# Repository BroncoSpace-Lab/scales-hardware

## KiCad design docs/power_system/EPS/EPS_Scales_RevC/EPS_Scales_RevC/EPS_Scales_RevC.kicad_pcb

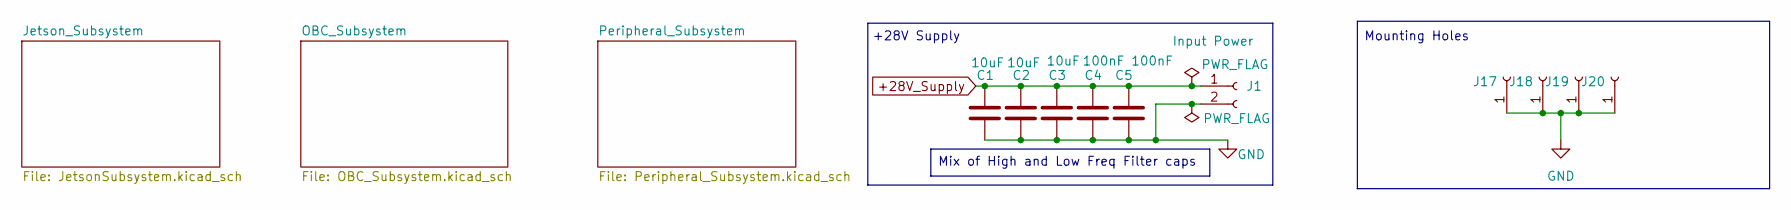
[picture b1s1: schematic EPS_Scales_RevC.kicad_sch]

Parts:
C1, C2, C3: 10uF; C_0603_1608Metric
C4, C5: 100nF; C_0603_1608Metric
J1: Input Power; AMASS_XT60PW-F_1x02_P7.20mm_Horizontal
J17, J18, J19, J20: Conn_01x01_Socket; MountingHole_2.7mm_M2.5_Pad_Via

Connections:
+28V_Supply: C1.1, C2.1, C3.1, C4.1, C5.1, J1.1; also elsewhere on the board
GND: C1.2, C2.2, C3.2, C4.2, C5.2, J1.2, J17.1, J18.1, J19.1, J20.1; also elsewhere on the board

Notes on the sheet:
Mounting Holes
+28V Supply
Mix of High and Low Freq Filter caps

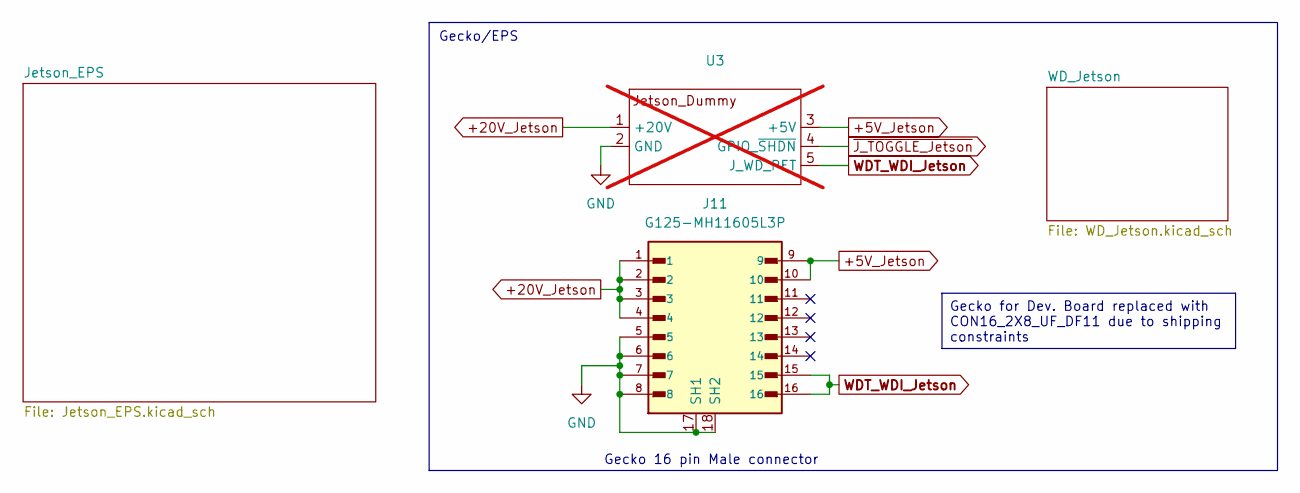
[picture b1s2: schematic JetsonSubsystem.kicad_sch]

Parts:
J11: G125-MH11605L3P; CON16_2X8_UF_DF11
U3: PinSocket_1x05_P2.54mm_Vertical; not fitted

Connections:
+5V_Jetson: J11.9, J11.10, U3.3 (+5V); also elsewhere on the board
+20V_Jetson: J11.1, J11.2, J11.3, J11.4, U3.1 (+20V); also elsewhere on the board
GND: J11.5, J11.6, J11.7, J11.8, J11.17 (SH1), J11.18 (SH2), U3.2 (GND); also elsewhere on the board
WDT_WDI_Jetson: J11.15, J11.16, U3.5 (J_WD_PET); also elsewhere on the board

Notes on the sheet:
Gecko 16 pin Male connector
Gecko/EPS
Gecko for Dev. Board replaced with CON16_2X8_UF_DF11 due to shipping constraints

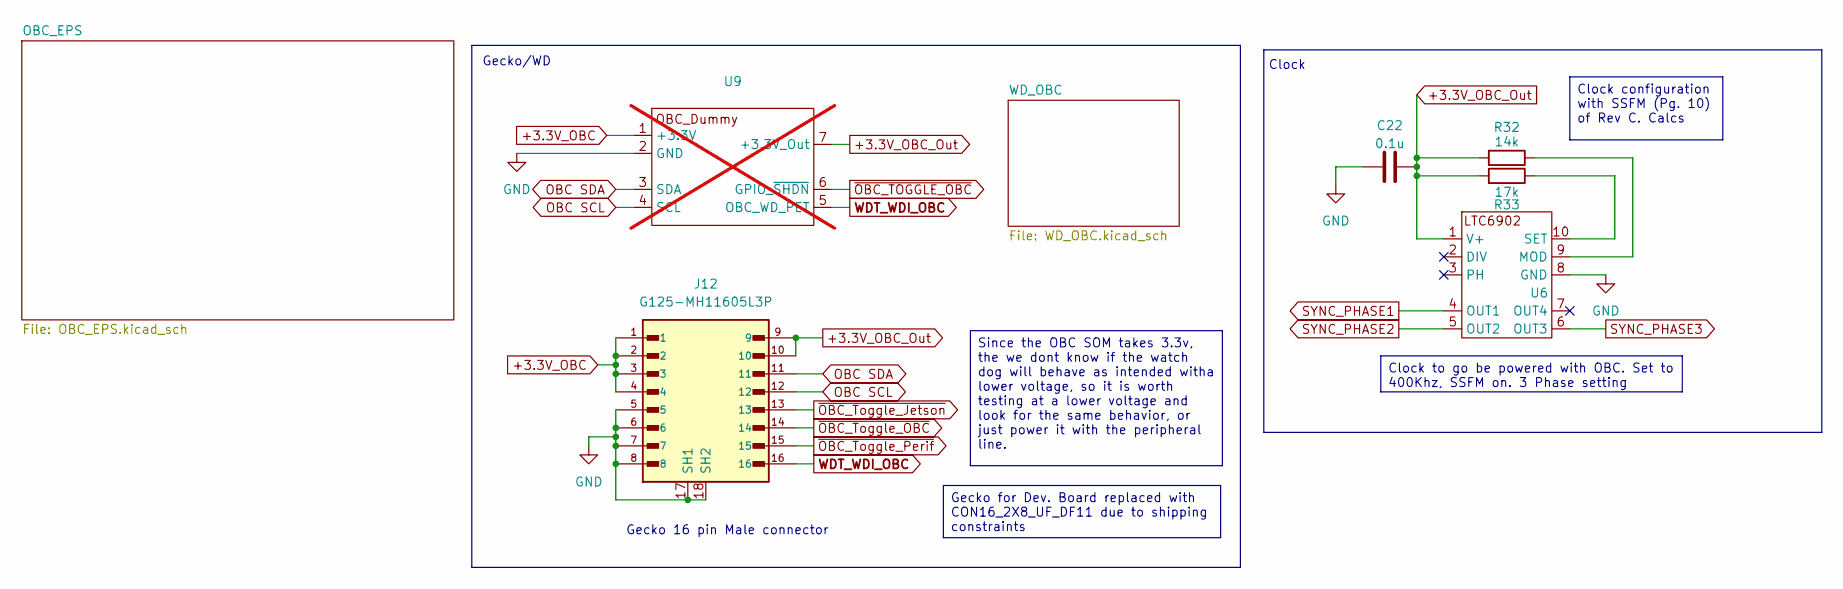
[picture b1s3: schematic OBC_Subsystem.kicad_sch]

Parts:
C22: 0.1u; C_0603_1608Metric
J12: G125-MH11605L3P; CON16_2X8_UF_DF11
R32: 14k; R_0603_1608Metric
R33: 17k; R_0603_1608Metric
U6: LTC6902
U9: PinSocket_1x07_P2.54mm_Vertical; not fitted

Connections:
+3.3V_OBC: J12.1, J12.2, J12.3, J12.4, U9.1 (+3.3V); also elsewhere on the board
+3.3V_OBC_Out: C22.2, J12.9, J12.10, R32.2, R33.2, U6.1 (V+), U9.7 (+3.3V_Out); also elsewhere on the board
GND: C22.1, J12.5, J12.6, J12.7, J12.8, J12.17 (SH1), J12.18 (SH2), U6.8 (GND), U9.2 (GND); also elsewhere on the board
unnamed: R32.1, U6.9 (MOD)
unnamed: R33.1, U6.10 (SET)
OBC SCL: J12.12, U9.4 (SCL); also elsewhere on the board
OBC SDA: J12.11, U9.3 (SDA); also elsewhere on the board
SYNC_PHASE1: U6.4 (OUT1); also elsewhere on the board
SYNC_PHASE2: U6.5 (OUT2); also elsewhere on the board
SYNC_PHASE3: U6.6 (OUT3); also elsewhere on the board
WDT_WDI_OBC: J12.16, U9.5 (OBC_WD_PET); also elsewhere on the board
~J_EN: J12.13; also elsewhere on the board
~OBC_EN: J12.14; also elsewhere on the board
~OBC_Toggle_Perif: J12.15; also elsewhere on the board

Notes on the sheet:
Clock
Gecko/WD
Gecko 16 pin Male connector
Since the OBC SOM takes 3.3v, the we dont know if the watch dog will behave as intended witha lower voltage, so it is worth testing at a lower voltage and look for the same behavior, or just power it with the peripheral line.
Gecko for Dev. Board replaced with CON16_2X8_UF_DF11 due to shipping constraints
Clock configuration with SSFM (Pg. 10) of Rev C. Calcs
Clock to go be powered with OBC. Set to 400Khz, SSFM on. 3 Phase setting

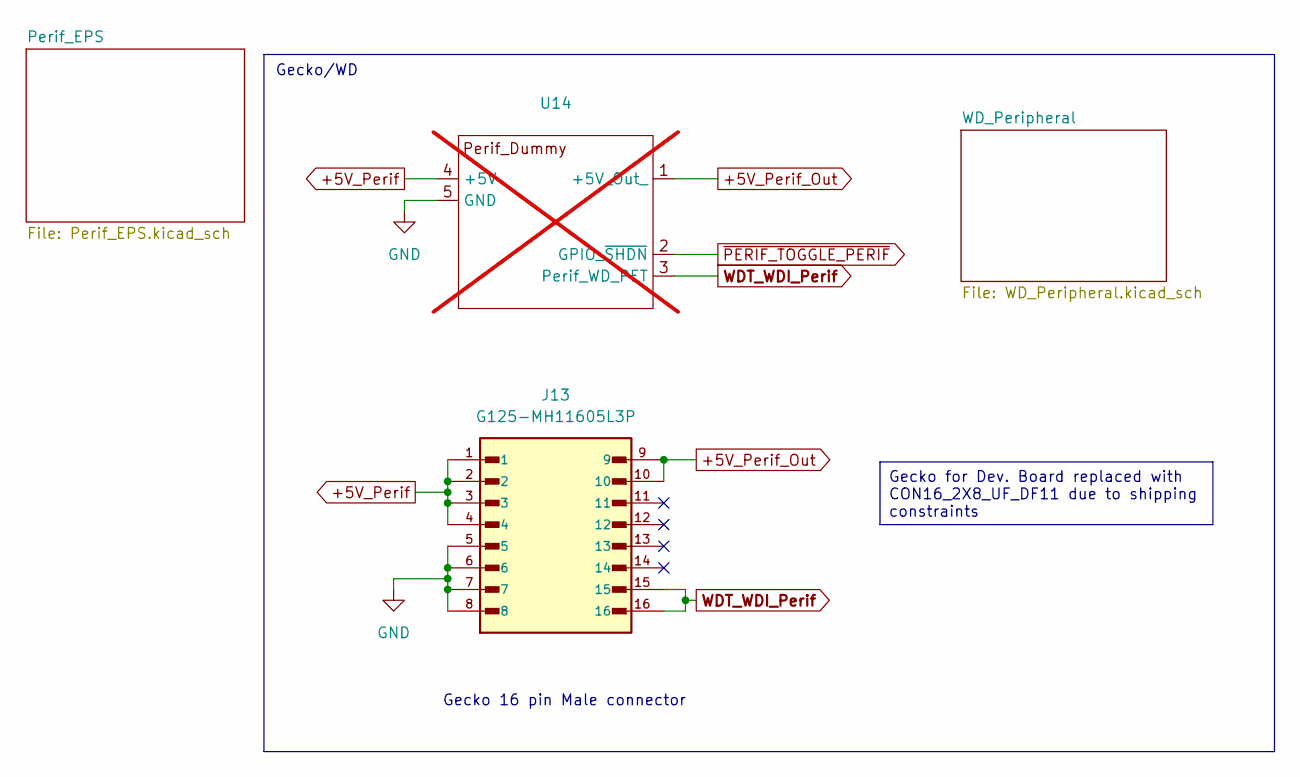
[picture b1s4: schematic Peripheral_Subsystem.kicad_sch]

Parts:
J13: G125-MH11605L3P; CON16_2X8_UF_DF11
U14: Perif. Board Dummy Connections; PinSocket_1x05_P2.54mm_Vertical; not fitted

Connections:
+5V_Perif: J13.1, J13.2, J13.3, J13.4, U14.4 (+5V); also elsewhere on the board
+5V_Perif_Out: J13.9, J13.10, U14.1 (+5V_Out_); also elsewhere on the board
GND: J13.5, J13.6, J13.7, J13.8, U14.5 (GND); also elsewhere on the board
WDT_WDI_Perif: J13.15, J13.16, U14.3 (Perif_WD_PET); also elsewhere on the board

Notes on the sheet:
Gecko/WD
Gecko 16 pin Male connector
Gecko for Dev. Board replaced with CON16_2X8_UF_DF11 due to shipping constraints

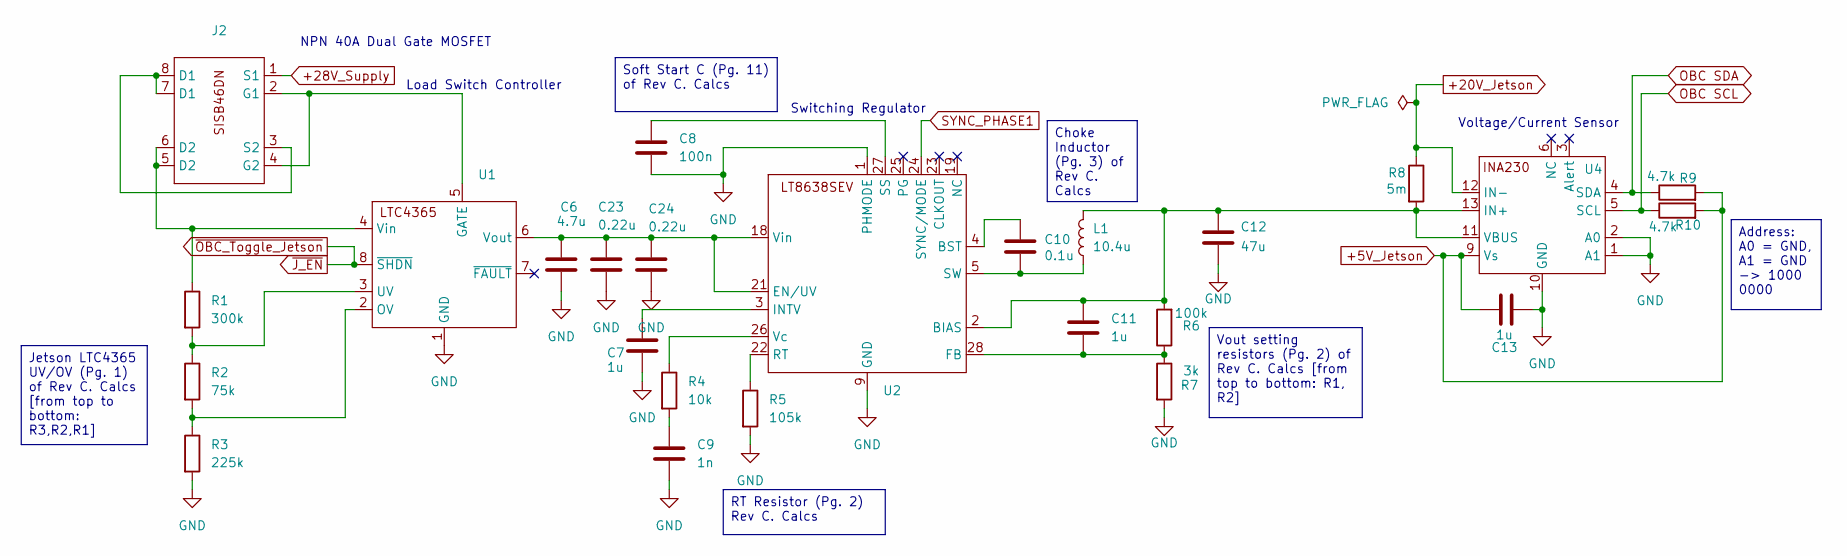
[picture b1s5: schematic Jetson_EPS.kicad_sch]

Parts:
C6: 4.7u; C_0603_1608Metric
C7, C11, C13: 1u; C_0603_1608Metric
C8: 100n; C_0603_1608Metric
C9: 1n; C_0603_1608Metric
C10: 0.1u; C_0603_1608Metric
C12: 47u; C_0603_1608Metric
C23, C24: 0.22u; C_0603_1608Metric
J2: MOSFET_DN-T1-GE3_VIS
L1: 10.4u; L_0603_1608Metric
R1: 300k; R_0603_1608Metric
R2: 75k; R_0603_1608Metric
R3: 225k; R_0603_1608Metric
R4: 10k; R_0603_1608Metric
R5: 105k; R_0603_1608Metric
R6: 100k; R_0603_1608Metric
R7: 3k; R_0603_1608Metric
R8: 5m; R_0603_1608Metric
R9, R10: 4.7k; R_0603_1608Metric
U1: LTC4365
U2: LT8638SEVPBF
U4: INA230; INA230AIRGTT

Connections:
+5V_Jetson: C13.2, R9.2, R10.2, U4.9 (Vs); also elsewhere on the board
+20V_Jetson: R8.1, U4.12 (IN-); also elsewhere on the board
+28V_Supply: J2.1 (S1); also elsewhere on the board
GND: C6.2, C7.2, C8.2, C9.2, C12.2, C13.1, C23.2, C24.2, R3.2, R5.2, R7.2, U1.1 (GND), U2.1 (PHMODE), U2.9 (GND), U4.1 (A1), U4.2 (A0), U4.10 (GND); also elsewhere on the board
unnamed: C9.1, R4.2
unnamed: J2.2 (G1), J2.4 (G2), U1.5 (GATE)
unnamed: J2.3 (S2), J2.7 (D1), J2.8 (D1)
unnamed: R2.2, R3.1, U1.2 (OV)
unnamed: R1.2, R2.1, U1.3 (UV)
unnamed: J2.5 (D2), J2.6 (D2), R1.1, U1.4 (Vin)
unnamed: C6.1, C23.1, C24.1, U1.6 (Vout), U2.18 (Vin), U2.21 (EN/UV)
unnamed: C11.1, C12.1, L1.2, R6.2, R8.2, U2.2 (BIAS), U4.11 (VBUS), U4.13 (IN+)
unnamed: C10.1, U2.4 (BST)
unnamed: C11.2, R6.1, R7.1, U2.28 (FB)
unnamed: C7.1, U2.3 (INTV)
unnamed: R5.1, U2.22 (RT)
unnamed: C8.1, U2.27 (SS)
unnamed: C10.2, L1.1, U2.5 (SW)
unnamed: R4.1, U2.26 (Vc)
OBC SCL: R10.1, U4.5 (SCL); also elsewhere on the board
OBC SDA: R9.1, U4.4 (SDA); also elsewhere on the board
SYNC_PHASE1: U2.24 (SYNC/MODE); also elsewhere on the board
~J_EN: U1.8 (~SHDN); also elsewhere on the board

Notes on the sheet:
Voltage/Current Sensor
Load Switch Controller
Switching Regulator
NPN 40A Dual Gate MOSFET
RT Resistor (Pg. 2) Rev C. Calcs
Jetson LTC4365 UV/OV (Pg. 1) of Rev C. Calcs [from top to bottom: R3,R2,R1]
Vout setting resistors (Pg. 2) of Rev C. Calcs [from top to bottom: R1, R2]
Choke Inductor (Pg. 3) of Rev C. Calcs
Address: A0 = GND, A1 = GND -> 1000 0000
Soft Start C (Pg. 11) of Rev C. Calcs

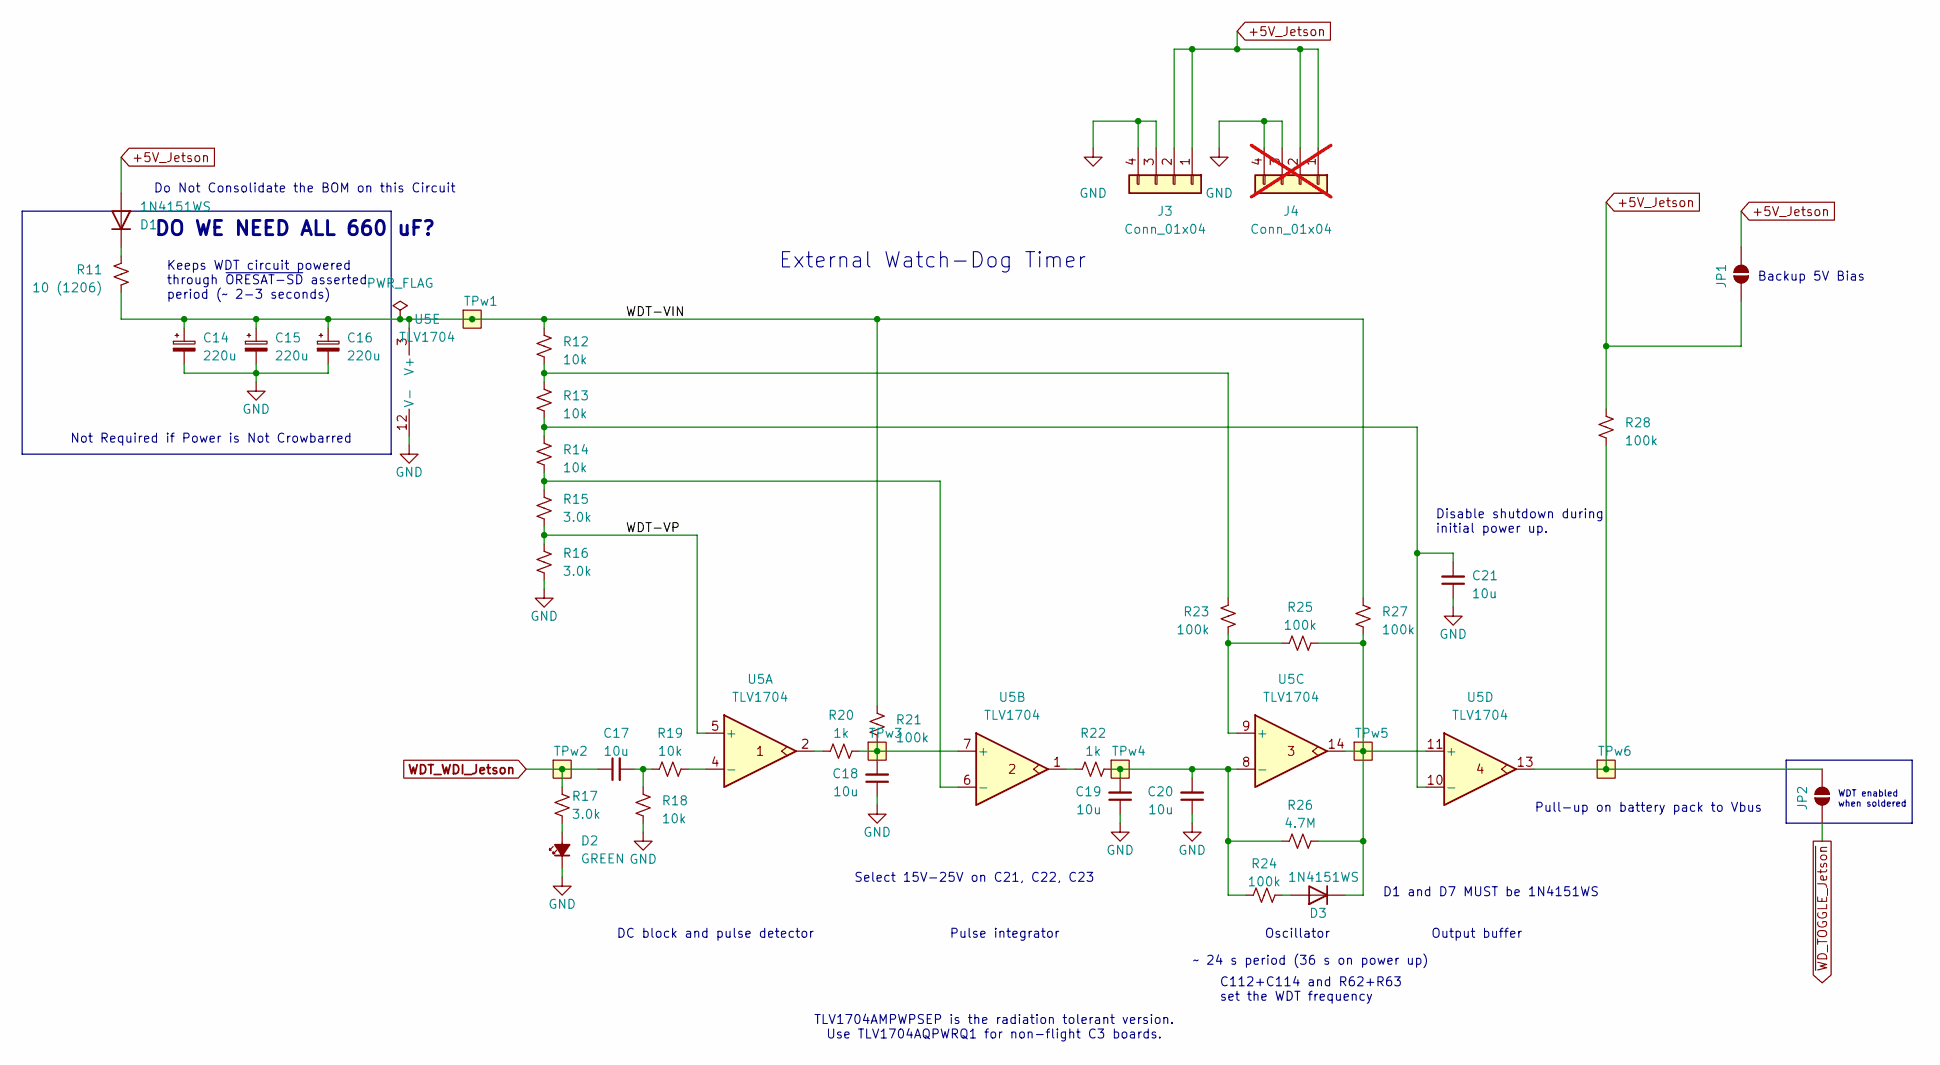
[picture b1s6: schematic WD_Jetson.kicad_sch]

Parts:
C14, C15, C16: 220u; CP_EIA-7361-38_AVX-V; MPN TCN4227M025R0100
C17, C18, C19, C20, C21: 10u; C_0603_1608Metric; MPN GRT188R61C106KE13D
D1, D3: 1N4151WS; D_SOD-323; MPN 1N4151WS-E3-08
D2: GREEN; LED_0603_1608Metric; MPN 150060GS75000
J3: Conn_01x04; PinSocket_1x04_P2.54mm_Vertical
J4: Conn_01x04; PinSocket_1x04_P2.54mm_Vertical; not fitted
JP1, JP2: SolderJumper_2_Open; SolderJumper-2_P1.3mm_Open_RoundedPad1.0x1.5mm
R11: 10 (1206); R_1206_3216Metric; MPN ESR18EZPF10R0
R12, R13, R14, R18, R19: 10k; R_0603_1608Metric; MPN RMCF0603FT10K0
R15, R16, R17: 3.0k; R_0603_1608Metric; MPN RMCF0603FT3K00
R20, R22: 1k; R_0603_1608Metric; MPN RMCF0603FT1K00
R21, R23, R24, R25, R27, R28: 100k; R_0603_1608Metric; MPN RMCF0603FT100K
R26: 4.7M; R_0603_1608Metric; MPN RMCF0603FT4M70
TPw1, TPw2, TPw3, TPw4, TPw5, TPw6: TestPoint-MinTH; TestPoint_Pad_1.0x1.0mm
U5: TLV1704; TSSOP-14_4.4x5mm_P0.65mm; MPN TLV1704AQPWRQ1

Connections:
+5V_Jetson: D1.2 (A), J3.1, J3.2, J4.1, J4.2, JP1.1 (A), JP1.2 (B), R28.2; also elsewhere on the board
/Jetson_Subsystem/WD_Jetson/WDT-VIN: C14.1, C15.1, C16.1, R11.2, R12.1, R21.1, R27.2, TPw1.1, U5.3 (V+)
/Jetson_Subsystem/WD_Jetson/WDT-VP: R15.2, R16.1, U5.5 (+)
GND: C14.2, C15.2, C16.2, C18.1, C19.1, C20.1, C21.1, D2.1 (K), J3.3, J3.4, J4.3, J4.4, R16.2, R18.2, U5.12 (V-); also elsewhere on the board
unnamed: C17.2, R18.1, R19.1
unnamed: D1.1 (K), R11.1
unnamed: D2.2 (A), R17.2
unnamed: D3.2 (A), R24.1
unnamed: D3.1 (K), R25.2, R26.1, R27.1, TPw5.1, U5.11 (+), U5.14
unnamed: JP2.1 (A), R28.1, TPw6.1, U5.13
unnamed: R12.2, R13.1, R23.2
unnamed: R20.1, U5.2
unnamed: R22.1, U5.1
unnamed: R19.2, U5.4 (-)
unnamed: C18.2, R20.2, R21.2, TPw3.1, U5.7 (+)
unnamed: R14.2, R15.1, U5.6 (-)
unnamed: R23.1, R25.1, U5.9 (+)
unnamed: C19.2, C20.2, R22.2, R24.2, R26.2, TPw4.1, U5.8 (-)
unnamed: C21.2, R13.2, R14.1, U5.10 (-)
WDT_WDI_Jetson: C17.1, R17.1, TPw2.1; also elsewhere on the board
~WD_TOGGLE_Jetson: JP2.2 (B)

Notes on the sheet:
TLV1704AMPWPSEP is the radiation tolerant version. Use TLV1704AQPWRQ1 for non-flight C3 boards.
Keeps WDT circuit powered through ~{ORESAT-SD} asserted period (~ 2-3 seconds)
Backup 5V Bias
Pull-up on battery pack to Vbus
Oscillator
External Watch-Dog Timer
Disable shutdown during initial power up.
Not Required if Power is Not Crowbarred
Pulse integrator
C112+C114 and R62+R63 set the WDT frequency
DO WE NEED ALL 660 uF?
~ 24 s period (36 s on power up)
D1 and D7 MUST be 1N4151WS
Do Not Consolidate the BOM on this Circuit
Select 15V-25V on C21, C22, C23
Output buffer
WDT enabled when soldered
DC block and pulse detector

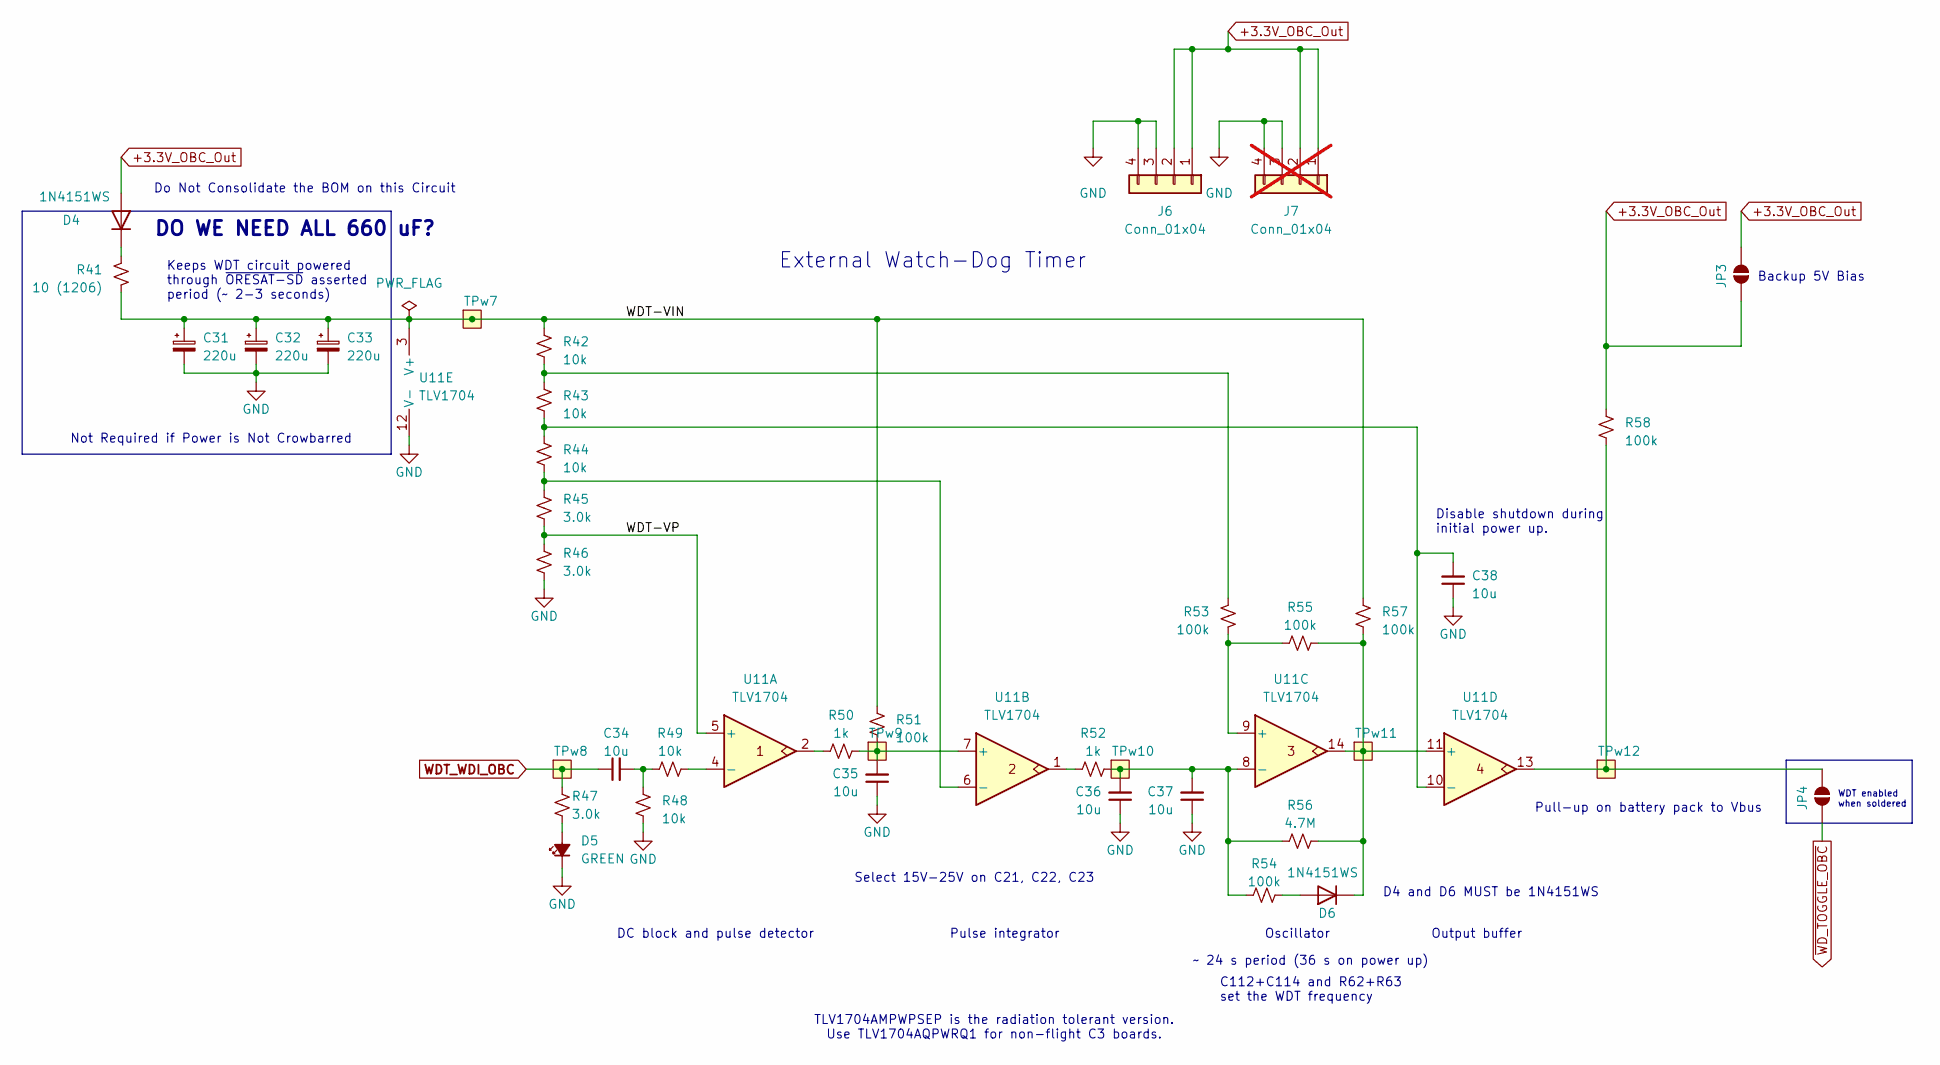
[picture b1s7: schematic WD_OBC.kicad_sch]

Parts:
C31, C32, C33: 220u; CP_EIA-7361-38_AVX-V; MPN TCN4227M025R0100
C34, C35, C36, C37, C38: 10u; C_0603_1608Metric; MPN GRT188R61C106KE13D
D4, D6: 1N4151WS; D_SOD-323; MPN 1N4151WS-E3-08
D5: GREEN; LED_0603_1608Metric; MPN 150060GS75000
J6: Conn_01x04; PinSocket_1x04_P2.54mm_Vertical
J7: Conn_01x04; PinSocket_1x04_P2.54mm_Vertical; not fitted
JP3, JP4: SolderJumper_2_Open; SolderJumper-2_P1.3mm_Open_RoundedPad1.0x1.5mm
R41: 10 (1206); R_1206_3216Metric; MPN ESR18EZPF10R0
R42, R43, R44, R48, R49: 10k; R_0603_1608Metric; MPN RMCF0603FT10K0
R45, R46, R47: 3.0k; R_0603_1608Metric; MPN RMCF0603FT3K00
R50, R52: 1k; R_0603_1608Metric; MPN RMCF0603FT1K00
R51, R53, R54, R55, R57, R58: 100k; R_0603_1608Metric; MPN RMCF0603FT100K
R56: 4.7M; R_0603_1608Metric; MPN RMCF0603FT4M70
TPw7, TPw8, TPw9, TPw10, TPw11, TPw12: TestPoint-MinTH; TestPoint_Pad_1.0x1.0mm
U11: TLV1704; TSSOP-14_4.4x5mm_P0.65mm; MPN TLV1704AQPWRQ1

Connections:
+3.3V_OBC_Out: D4.2 (A), J6.1, J6.2, J7.1, J7.2, JP3.1 (A), JP3.2 (B), R58.2; also elsewhere on the board
/OBC_Subsystem/WD_OBC/WDT-VIN: C31.1, C32.1, C33.1, R41.2, R42.1, R51.1, R57.2, TPw7.1, U11.3 (V+)
/OBC_Subsystem/WD_OBC/WDT-VP: R45.2, R46.1, U11.5 (+)
GND: C31.2, C32.2, C33.2, C35.1, C36.1, C37.1, C38.1, D5.1 (K), J6.3, J6.4, J7.3, J7.4, R46.2, R48.2, U11.12 (V-); also elsewhere on the board
unnamed: C34.2, R48.1, R49.1
unnamed: D4.1 (K), R41.1
unnamed: D5.2 (A), R47.2
unnamed: D6.2 (A), R54.1
unnamed: D6.1 (K), R55.2, R56.1, R57.1, TPw11.1, U11.11 (+), U11.14
unnamed: JP4.1 (A), R58.1, TPw12.1, U11.13
unnamed: R42.2, R43.1, R53.2
unnamed: R50.1, U11.2
unnamed: R52.1, U11.1
unnamed: R49.2, U11.4 (-)
unnamed: C35.2, R50.2, R51.2, TPw9.1, U11.7 (+)
unnamed: R44.2, R45.1, U11.6 (-)
unnamed: R53.1, R55.1, U11.9 (+)
unnamed: C36.2, C37.2, R52.2, R54.2, R56.2, TPw10.1, U11.8 (-)
unnamed: C38.2, R43.2, R44.1, U11.10 (-)
WDT_WDI_OBC: C34.1, R47.1, TPw8.1; also elsewhere on the board
~WD_TOGGLE_OBC: JP4.2 (B)

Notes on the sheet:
TLV1704AMPWPSEP is the radiation tolerant version. Use TLV1704AQPWRQ1 for non-flight C3 boards.
Keeps WDT circuit powered through ~{ORESAT-SD} asserted period (~ 2-3 seconds)
Backup 5V Bias
Pull-up on battery pack to Vbus
Oscillator
External Watch-Dog Timer
Disable shutdown during initial power up.
Not Required if Power is Not Crowbarred
Pulse integrator
C112+C114 and R62+R63 set the WDT frequency
DO WE NEED ALL 660 uF?
~ 24 s period (36 s on power up)
D4 and D6 MUST be 1N4151WS
Do Not Consolidate the BOM on this Circuit
Select 15V-25V on C21, C22, C23
Output buffer
WDT enabled when soldered
DC block and pulse detector

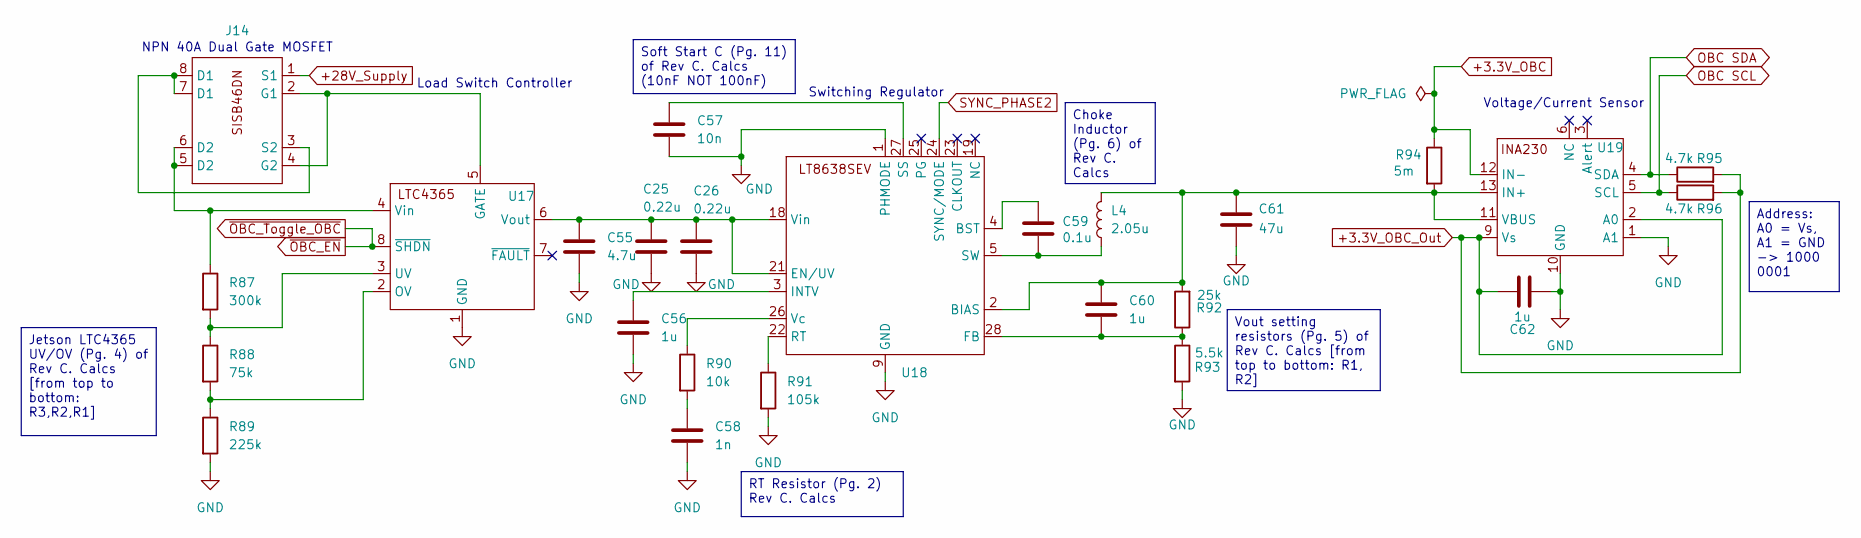
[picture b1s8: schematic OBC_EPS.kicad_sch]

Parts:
C25, C26: 0.22u; C_0603_1608Metric
C55: 4.7u; C_0603_1608Metric
C56, C60, C62: 1u; C_0603_1608Metric
C57: 10n; C_0603_1608Metric
C58: 1n; C_0603_1608Metric
C59: 0.1u; C_0603_1608Metric
C61: 47u; C_0603_1608Metric
J14: MOSFET_DN-T1-GE3_VIS
L4: 2.05u; L_0603_1608Metric
R87: 300k; R_0603_1608Metric
R88: 75k; R_0603_1608Metric
R89: 225k; R_0603_1608Metric
R90: 10k; R_0603_1608Metric
R91: 105k; R_0603_1608Metric
R92: 25k; R_0603_1608Metric
R93: 5.5k; R_0603_1608Metric
R94: 5m; R_0603_1608Metric
R95, R96: 4.7k; R_0603_1608Metric
U17: LTC4365
U18: LT8638SEVPBF
U19: INA230; INA230AIRGTT

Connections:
+3.3V_OBC: R94.1, U19.12 (IN-); also elsewhere on the board
+3.3V_OBC_Out: C62.2, R95.2, R96.2, U19.2 (A0), U19.9 (Vs); also elsewhere on the board
+28V_Supply: J14.1 (S1); also elsewhere on the board
GND: C25.2, C26.2, C55.2, C56.2, C57.2, C58.2, C61.2, C62.1, R89.2, R91.2, R93.2, U17.1 (GND), U18.1 (PHMODE), U18.9 (GND), U19.1 (A1), U19.10 (GND); also elsewhere on the board
unnamed: C58.1, R90.2
unnamed: J14.2 (G1), J14.4 (G2), U17.5 (GATE)
unnamed: J14.3 (S2), J14.7 (D1), J14.8 (D1)
unnamed: R88.2, R89.1, U17.2 (OV)
unnamed: R87.2, R88.1, U17.3 (UV)
unnamed: J14.5 (D2), J14.6 (D2), R87.1, U17.4 (Vin)
unnamed: C25.1, C26.1, C55.1, U17.6 (Vout), U18.18 (Vin), U18.21 (EN/UV)
unnamed: C60.1, C61.1, L4.2, R92.2, R94.2, U18.2 (BIAS), U19.11 (VBUS), U19.13 (IN+)
unnamed: C59.1, U18.4 (BST)
unnamed: C60.2, R92.1, R93.1, U18.28 (FB)
unnamed: C56.1, U18.3 (INTV)
unnamed: R91.1, U18.22 (RT)
unnamed: C57.1, U18.27 (SS)
unnamed: C59.2, L4.1, U18.5 (SW)
unnamed: R90.1, U18.26 (Vc)
OBC SCL: R96.1, U19.5 (SCL); also elsewhere on the board
OBC SDA: R95.1, U19.4 (SDA); also elsewhere on the board
SYNC_PHASE2: U18.24 (SYNC/MODE); also elsewhere on the board
~OBC_EN: U17.8 (~SHDN); also elsewhere on the board

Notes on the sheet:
Switching Regulator
Voltage/Current Sensor
NPN 40A Dual Gate MOSFET
Load Switch Controller
Soft Start C (Pg. 11) of Rev C. Calcs (10nF NOT 100nF)
RT Resistor (Pg. 2) Rev C. Calcs
Choke Inductor (Pg. 6) of Rev C. Calcs
Vout setting resistors (Pg. 5) of Rev C. Calcs [from top to bottom: R1, R2]
Jetson LTC4365 UV/OV (Pg. 4) of Rev C. Calcs [from top to bottom: R3,R2,R1]
Address: A0 = Vs, A1 = GND -> 1000 0001

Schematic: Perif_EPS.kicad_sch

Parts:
C27, C28: 0.22u; C_0603_1608Metric
C63: 4.7u; C_0603_1608Metric
C64, C68, C70: 1u; C_0603_1608Metric
C65: 20nF; C_0603_1608Metric
C66: 1n; C_0603_1608Metric
C67: 0.1u; C_0603_1608Metric
C69: 47u; C_0603_1608Metric
J15: MOSFET_DN-T1-GE3_VIS
L5: 2.9u; L_0603_1608Metric
R97: 300k; R_0603_1608Metric
R98: 75k; R_0603_1608Metric
R99: 225k; R_0603_1608Metric
R100: 10k; R_0603_1608Metric
R101: 105k; R_0603_1608Metric
R102: 22k; R_0603_1608Metric
R103: 3k; R_0603_1608Metric
R104: 5m; R_0603_1608Metric
R105, R106: 4.7k; R_0603_1608Metric
U20: LTC4365
U21: LT8638SEVPBF
U22: INA230; INA230AIRGTT

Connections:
+5V_Perif: R104.1, U22.12 (IN-); also elsewhere on the board
+5V_Perif_Out: C70.2, R105.2, R106.2, U22.9 (Vs); also elsewhere on the board
+28V_Supply: J15.1 (S1); also elsewhere on the board
GND: C27.2, C28.2, C63.2, C64.2, C65.2, C66.2, C69.2, C70.1, R99.2, R101.2, R103.2, U20.1 (GND), U21.1 (PHMODE), U21.9 (GND), U22.1 (A1), U22.10 (GND); also elsewhere on the board
unnamed: C66.1, R100.2
unnamed: J15.2 (G1), J15.4 (G2), U20.5 (GATE)
unnamed: J15.3 (S2), J15.7 (D1), J15.8 (D1)
unnamed: R98.2, R99.1, U20.2 (OV)
unnamed: R97.2, R98.1, U20.3 (UV)
unnamed: J15.5 (D2), J15.6 (D2), R97.1, U20.4 (Vin)
unnamed: C27.1, C28.1, C63.1, U20.6 (Vout), U21.18 (Vin), U21.21 (EN/UV)
unnamed: C68.1, C69.1, L5.2, R102.2, R104.2, U21.2 (BIAS), U22.11 (VBUS), U22.13 (IN+)
unnamed: C67.1, U21.4 (BST)
unnamed: C68.2, R102.1, R103.1, U21.28 (FB)
unnamed: C64.1, U21.3 (INTV)
unnamed: R101.1, U21.22 (RT)
unnamed: C65.1, U21.27 (SS)
unnamed: C67.2, L5.1, U21.5 (SW)
unnamed: R100.1, U21.26 (Vc)
OBC SCL: R106.1, U22.5 (SCL); also elsewhere on the board
OBC SDA: R105.1, U22.2 (A0), U22.4 (SDA); also elsewhere on the board
SYNC_PHASE3: U21.24 (SYNC/MODE); also elsewhere on the board
~OBC_Toggle_Perif: U20.8 (~SHDN); also elsewhere on the board

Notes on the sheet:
Voltage/Current Sensor
NPN 40A Dual Gate MOSFET
Load Switch Controller
Switching Regulator
Vout setting resistors (Pg. 5) of Rev C. Calcs [from top to bottom: R1, R2]
Peripheral LTC4365 UV/OV (Pg. 7) of Rev C. Calcs [from top to bottom: R3,R2,R1]
RT Resistor (Pg. 2) Rev C. Calcs
Soft Start C (Pg. 11) of Rev C. Calcs
Choke Inductor (Pg. 9) of Rev C. Calcs
Address: A0 = SDA, A1 = GND -> 1000 0010

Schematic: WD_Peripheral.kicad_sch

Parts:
C47, C48, C49: 220u; CP_EIA-7361-38_AVX-V; MPN TCN4227M025R0100
C50, C51, C52, C53, C54: 10u; C_0603_1608Metric; MPN GRT188R61C106KE13D
D7, D9: 1N4151WS; D_SOD-323; MPN 1N4151WS-E3-08
D8: GREEN; LED_0603_1608Metric; MPN 150060GS75000
J9: Conn_01x04; PinSocket_1x04_P2.54mm_Vertical
J10: Conn_01x04; PinSocket_1x04_P2.54mm_Vertical; not fitted
JP5, JP6: SolderJumper_2_Open; SolderJumper-2_P1.3mm_Open_RoundedPad1.0x1.5mm
R69: 10 (1206); R_1206_3216Metric; MPN ESR18EZPF10R0
R70, R71, R72, R76, R77: 10k; R_0603_1608Metric; MPN RMCF0603FT10K0
R73, R74, R75: 3.0k; R_0603_1608Metric; MPN RMCF0603FT3K00
R78, R80: 1k; R_0603_1608Metric; MPN RMCF0603FT1K00
R79, R81, R82, R83, R85, R86: 100k; R_0603_1608Metric; MPN RMCF0603FT100K
R84: 4.7M; R_0603_1608Metric; MPN RMCF0603FT4M70
TPw13, TPw14, TPw15, TPw16, TPw17, TPw18: TestPoint-MinTH; TestPoint_Pad_1.0x1.0mm
U16: TLV1704; TSSOP-14_4.4x5mm_P0.65mm; MPN TLV1704AQPWRQ1

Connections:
+5V_Perif_Out: D7.2 (A), J9.1, J9.2, J10.1, J10.2, JP5.1 (A), JP5.2 (B), R86.2; also elsewhere on the board
/Peripheral_Subsystem/WD_Peripheral/WDT-VIN: C47.1, C48.1, C49.1, R69.2, R70.1, R79.1, R85.2, TPw13.1, U16.3 (V+)
/Peripheral_Subsystem/WD_Peripheral/WDT-VP: R73.2, R74.1, U16.5 (+)
GND: C47.2, C48.2, C49.2, C51.1, C52.1, C53.1, C54.1, D8.1 (K), J9.3, J9.4, J10.3, J10.4, R74.2, R76.2, U16.12 (V-); also elsewhere on the board
unnamed: C50.2, R76.1, R77.1
unnamed: D7.1 (K), R69.1
unnamed: D8.2 (A), R75.2
unnamed: D9.2 (A), R82.1
unnamed: D9.1 (K), R83.2, R84.1, R85.1, TPw17.1, U16.11 (+), U16.14
unnamed: JP6.1 (A), R86.1, TPw18.1, U16.13
unnamed: R70.2, R71.1, R81.2
unnamed: R78.1, U16.2
unnamed: R80.1, U16.1
unnamed: R77.2, U16.4 (-)
unnamed: C51.2, R78.2, R79.2, TPw15.1, U16.7 (+)
unnamed: R72.2, R73.1, U16.6 (-)
unnamed: R81.1, R83.1, U16.9 (+)
unnamed: C52.2, C53.2, R80.2, R82.2, R84.2, TPw16.1, U16.8 (-)
unnamed: C54.2, R71.2, R72.1, U16.10 (-)
WDT_WDI_Perif: C50.1, R75.1, TPw14.1; also elsewhere on the board
~OBC_Toggle_Perif: JP6.2 (B); also elsewhere on the board

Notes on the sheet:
TLV1704AMPWPSEP is the radiation tolerant version. Use TLV1704AQPWRQ1 for non-flight C3 boards.
Keeps WDT circuit powered through ~{ORESAT-SD} asserted period (~ 2-3 seconds)
Backup 5V Bias
Pull-up on battery pack to Vbus
Oscillator
External Watch-Dog Timer
Disable shutdown during initial power up.
Not Required if Power is Not Crowbarred
Pulse integrator
C112+C114 and R62+R63 set the WDT frequency
DO WE NEED ALL 660 uF?
~ 24 s period (36 s on power up)
D5 and D7 MUST be 1N4151WS
Do Not Consolidate the BOM on this Circuit
Select 15V-25V on C21, C22, C23
Output buffer
WDT enabled when soldered
DC block and pulse detector

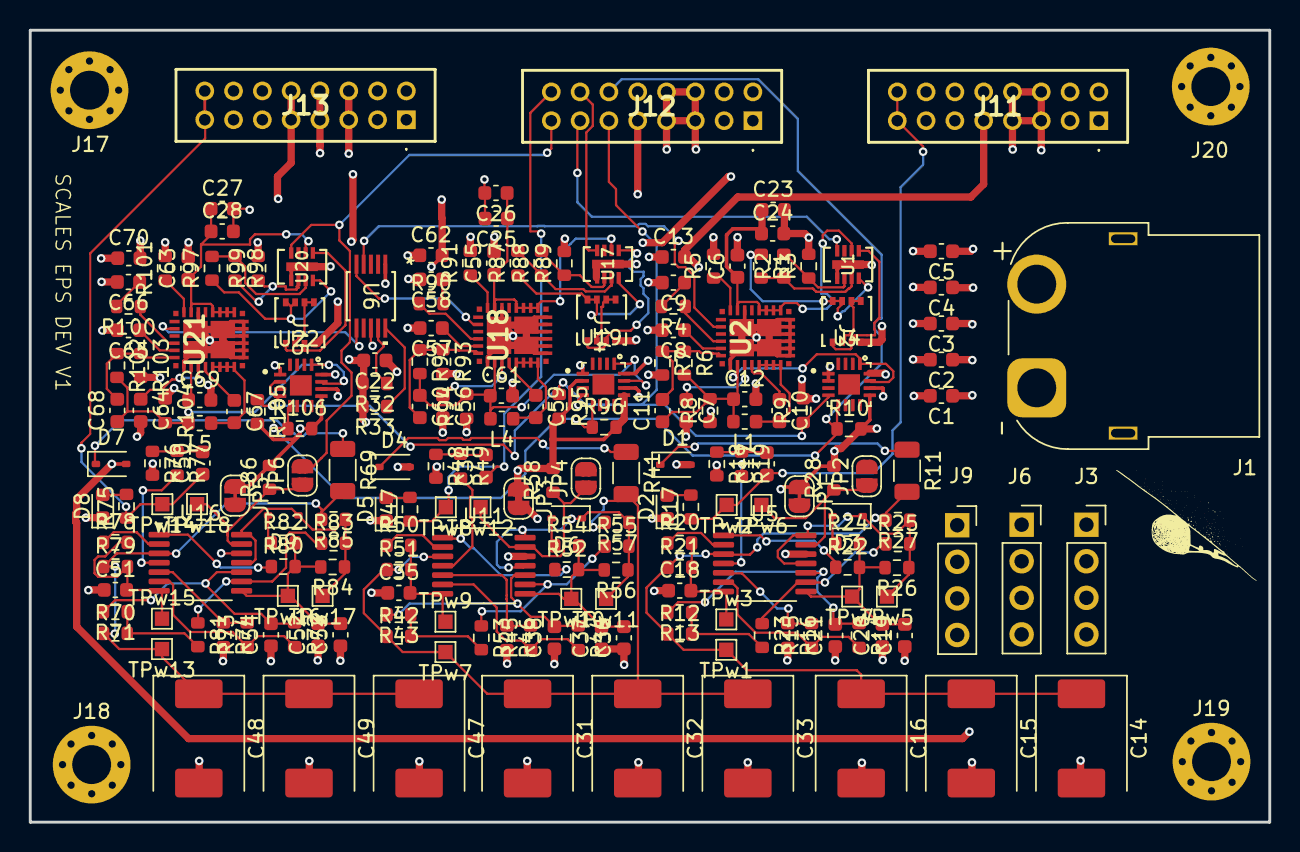
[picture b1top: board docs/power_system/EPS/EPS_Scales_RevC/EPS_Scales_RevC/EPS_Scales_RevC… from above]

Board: 4 copper layers, 86.1 x 55.0 mm, 209 parts (0 on the bottom side), 117 nets.

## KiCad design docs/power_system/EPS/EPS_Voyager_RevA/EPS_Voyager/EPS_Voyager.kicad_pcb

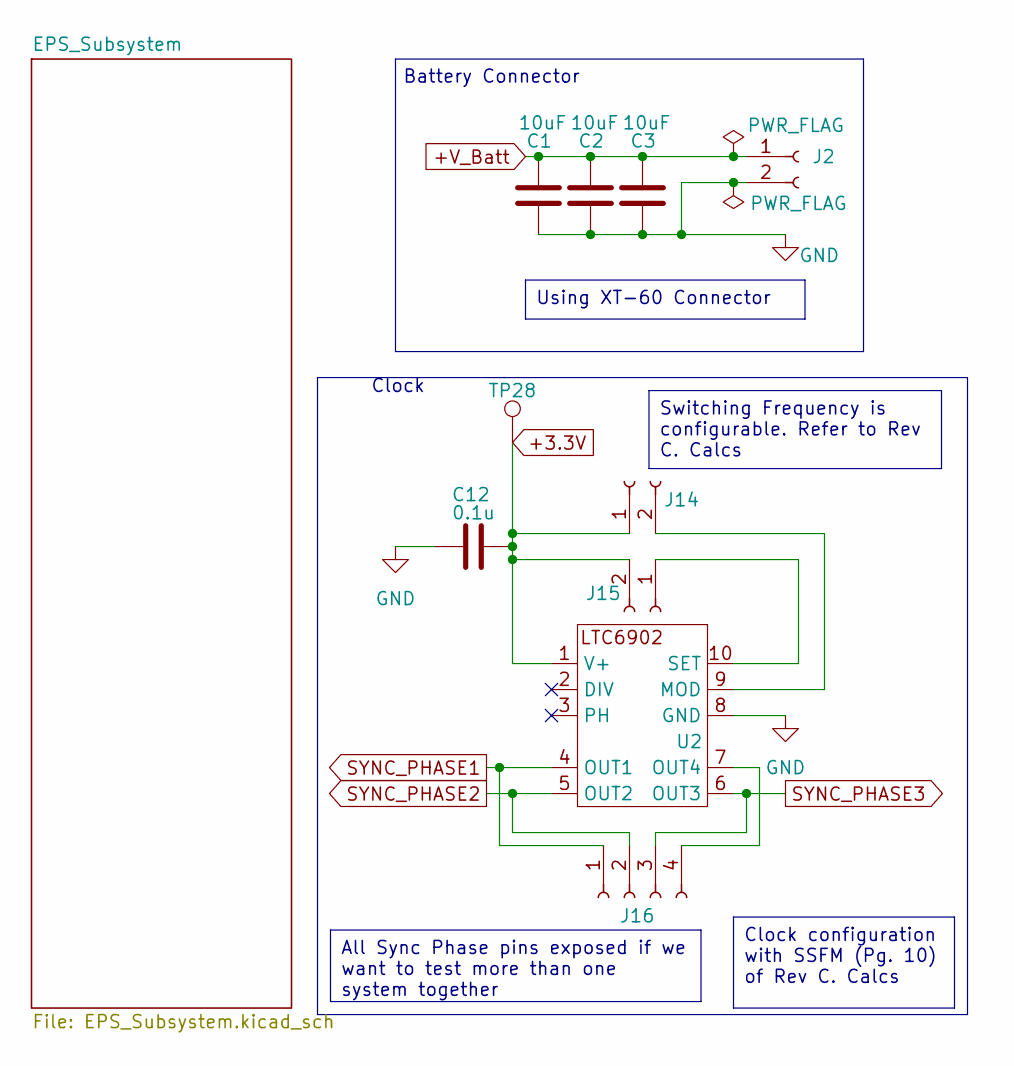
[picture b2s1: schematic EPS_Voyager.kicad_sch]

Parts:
C1, C2, C3: 10uF; C_1210_3225Metric
C12: 0.1u; C_1210_3225Metric
J2: Input Power; AMASS_XT60PW-F_1x02_P7.20mm_Horizontal
J14, J15: Conn_01x02_Socket; PinSocket_1x02_P2.54mm_Vertical
J16: Conn_01x04_Socket; PinSocket_1x04_P2.54mm_Vertical
TP28: TestPoint; TestPoint_Pad_1.0x1.0mm
U2: LTC6902

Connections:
+3.3V: C12.2, J14.1, J15.2, TP28.1, U2.1 (V+); also elsewhere on the board
+V_Batt: C1.1, C2.1, C3.1, J2.1; also elsewhere on the board
GND: C1.2, C2.2, C3.2, C12.1, J2.2, U2.8 (GND); also elsewhere on the board
unnamed: J14.2, U2.9 (MOD)
unnamed: J15.1, U2.10 (SET)
unnamed: J16.4, U2.7 (OUT4)
SYNC_PHASE1: J16.1, U2.4 (OUT1)
SYNC_PHASE2: J16.2, U2.5 (OUT2)
SYNC_PHASE3: J16.3, U2.6 (OUT3)

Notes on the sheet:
Clock
Battery Connector
Switching Frequency is configurable. Refer to Rev C. Calcs
Clock configuration with SSFM (Pg. 10) of Rev C. Calcs
Using XT-60 Connector
All Sync Phase pins exposed if we want to test more than one system together
